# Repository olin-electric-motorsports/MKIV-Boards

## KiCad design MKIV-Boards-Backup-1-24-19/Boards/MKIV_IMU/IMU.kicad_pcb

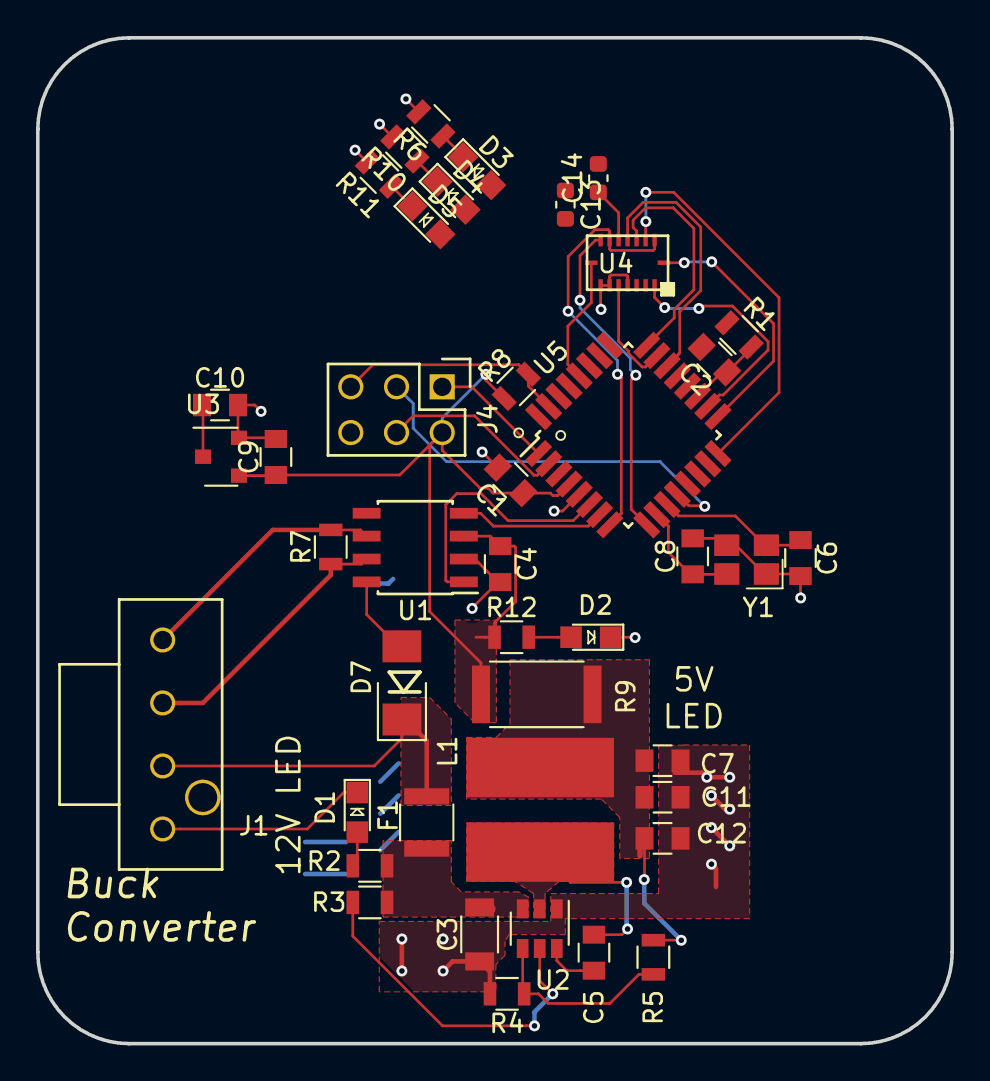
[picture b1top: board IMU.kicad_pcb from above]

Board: 2 copper layers, 50.8 x 55.9 mm, 42 parts (0 on the bottom side), 38 nets.

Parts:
C1, C4, C5, C9, C10, C12: C_0.1uF; C_0805_OEM
C2: C_100pF; C_0805_OEM
C3: C_22uF; C_1206_OEM
C6, C8: C_30pF; C_0805_OEM
C7: C_47uF; C_0805_OEM
C11: C_1uF; C_0805_OEM
C13, C14: C_100nF; C_0603_1608Metric
D1, D2, D3, D4, D5: LED_0805; LED_0805_OEM
D7: D_Zener_18V; DO-214AA
F1: 500mA; Fuse_1210
J1: UF_4_VT; Ultrafit_4
J4: CONN_02X03; Pin_Header_Straight_2x03
L1: L_4.7uH; 4.7uH_Inductor_OEM
R1: R_100; R_0805_OEM
R2: R_1k; R_0805_OEM
R3, R4, R8: R_10k; R_0805_OEM
R5: R_51.1k; R_0805_OEM
R6, R10, R11, R12: R_200; R_0805_OEM
R7: R_120; R_0805_OEM
R9: R_0_Jumper; R_2512_OEM
U1: CAN_Transceiver; SOIC-8_3.9x4.9mm_Pitch1.27mm_OEM
U2: TPS561201; SOT-23-6_OEM
U3: LM3480; SOT-23-3_OEM
U4: BMI088; bmi088
U5: ATMEGA16M1; TQFP-32_7x7mm_Pitch0.8mm
Y1: Crystal_SMD; Crystal_SMD_FA238

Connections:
/3.3V: C10.1, C13.2, C14.1, U3.1, U4.3, U4.11
/12V: D7.1, F1.1, J1.2
/12V_Fused: C3.1, F1.2, R2.1, R3.1, U2.3
/CANH: J1.3, R7.1, U1.7
/CANL: J1.4, R7.2, U1.6
/CS_ACCEL: U4.14, U5.16
/CS_GYRO: U4.5, U5.23
/INT1: U4.16, U5.17
/INT2: U4.1, U5.18
/INT3: U4.12, U5.22
/INT4: U4.13, U5.24
/MISO: J4.1, U5.1
/MISO2: U4.10, U4.15, U5.8
/MOSI: J4.4, U5.2
/MOSI2: U4.9, U5.9
/PLED1: D3.2, U5.25
/PLED2: D4.2, U5.26
/PLED3: D5.2, U5.27
/RESET: J4.5, R8.2, U5.31
/RXCAN: U1.4, U5.7
/SCK: J4.3, U5.12
/SCK2: U4.8, U5.28
/TXCAN: U1.1, U5.6
GND: C1.2, C2.2, C3.2, C4.2, C6.2, C7.2, C8.2, C9.2, C10.2, C11.2, C12.2, C13.1, C14.2, D1.1, D2.1, D7.2, J1.1, J4.6, R4.2, R6.2, R10.2, R11.2, U1.2, U1.8, U2.1, U3.3, U4.4, U4.6, U4.7, U5.5, U5.20, Y1.2, Y1.4
unnamed: C2.1, R1.2, U5.19
unnamed: C5.1, U2.6
unnamed: C5.2, L1.1, U2.2
unnamed: C6.1, U5.11, Y1.1
unnamed: C8.1, U5.10, Y1.3
unnamed: C7.1, C11.1, C12.1, L1.2, R5.2, R9.2
unnamed: D1.2, R2.2
unnamed: D2.2, R12.2
unnamed: D3.1, R6.1
unnamed: D4.1, R10.1
unnamed: D5.1, R11.1
unnamed: R3.2, U2.5
unnamed: R4.1, R5.1, U2.4
VCC: C1.1, C4.1, C9.1, J4.2, R1.1, R8.1, R9.1, R12.1, U1.3, U3.2, U5.4
